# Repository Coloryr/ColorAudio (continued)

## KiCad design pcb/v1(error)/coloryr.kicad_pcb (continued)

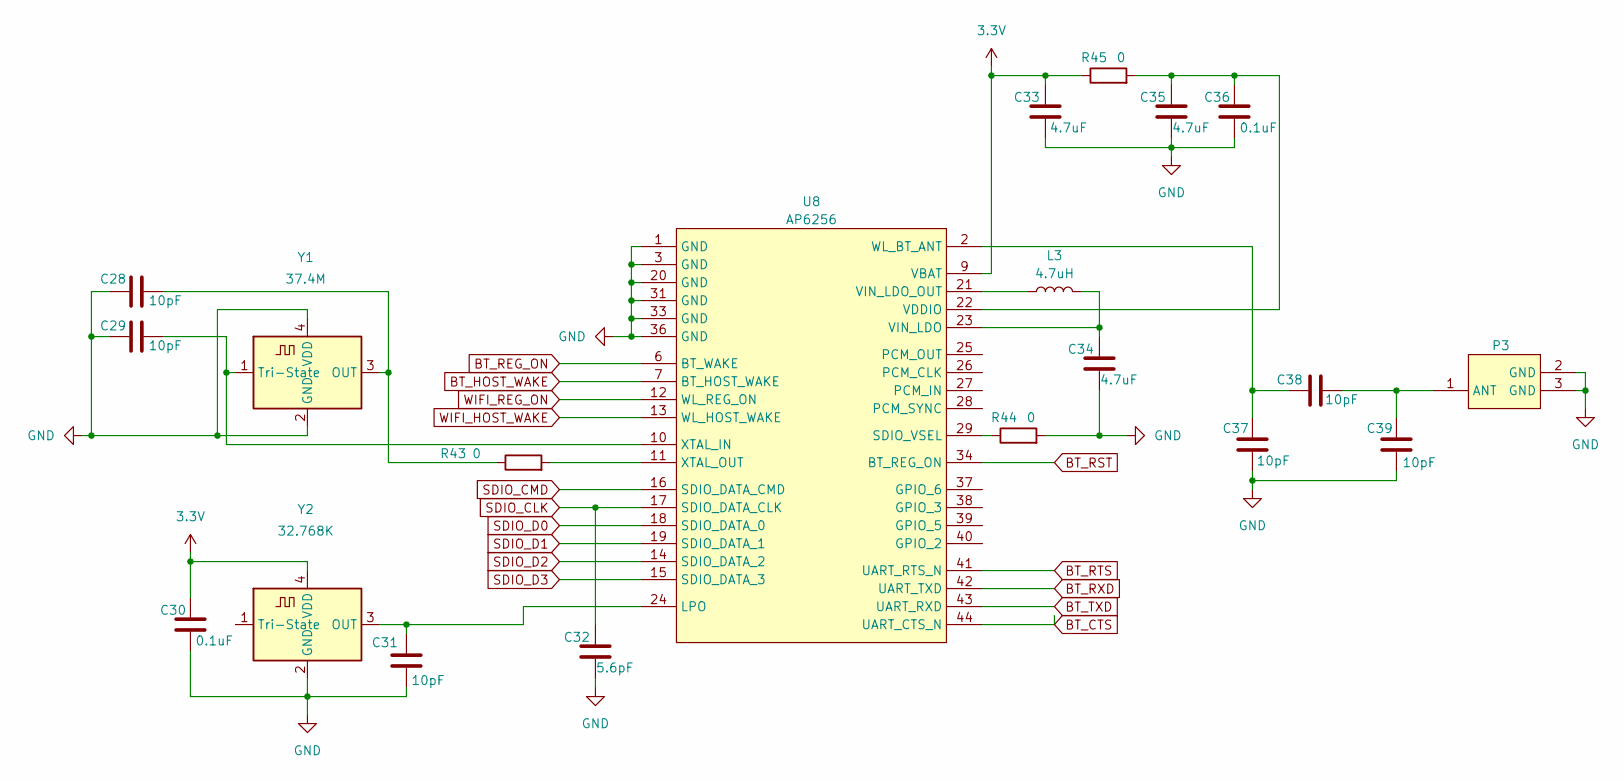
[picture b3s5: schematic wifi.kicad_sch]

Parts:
C28, C29, C31, C37, C38, C39: 10pF; C_0402_1005Metric_Pad0.74x0.62mm_HandSolder
C30, C36: 0.1uF; C_0402_1005Metric_Pad0.74x0.62mm_HandSolder
C32: 5.6pF; C_0402_1005Metric_Pad0.74x0.62mm_HandSolder
C33, C34, C35: 4.7uF; C_0402_1005Metric_Pad0.74x0.62mm_HandSolder
L3: 4.7uH; L_Murata_LQH2MCNxxxx02_2.0x1.6mm
P3: IPEX-SMD_BWIPX-1-001E
R43, R44, R45: 0; R_0402_1005Metric_Pad0.72x0.64mm_HandSolder
U8: AP6256
Y1: 37.4M; Oscillator_SMD_ECS_2520MV-xxx-xx-4Pin_2.5x2.0mm
Y2: 32.768K; Oscillator_SMD_ECS_2520MV-xxx-xx-4Pin_2.5x2.0mm

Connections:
3.3V: C30.2, C33.1, R45.1, U8.9 (VBAT), Y2.4 (VDD); also elsewhere on the board
BT_CTS: U8.44 (UART_CTS_N); also elsewhere on the board
BT_HOST_WAKE: U8.7 (BT_HOST_WAKE); also elsewhere on the board
BT_REG_ON: U8.6 (BT_WAKE); also elsewhere on the board
BT_RST: U8.34 (BT_REG_ON); also elsewhere on the board
BT_RTS: U8.41 (UART_RTS_N); also elsewhere on the board
BT_RXD: U8.42 (UART_TXD); also elsewhere on the board
BT_TXD: U8.43 (UART_RXD); also elsewhere on the board
GND: C28.1, C29.1, C30.1, C31.1, C32.2, C33.2, C34.2, C35.2, C36.1, C37.2, C39.2, P3.2 (GND), P3.3 (GND), R44.2, U8.1 (GND), U8.3 (GND), U8.20 (GND), U8.31 (GND), U8.33 (GND), U8.36 (GND), Y1.2 (GND), Y1.4 (VDD), Y2.2 (GND); also elsewhere on the board
unnamed: C38.1, C39.1, P3.1 (ANT)
unnamed: C31.2, U8.24 (LPO), Y2.3 (OUT)
unnamed: R44.1, U8.29 (SDIO_VSEL)
unnamed: C35.1, C36.2, R45.2, U8.22 (VDDIO)
unnamed: C34.1, L3.2, U8.23 (VIN_LDO)
unnamed: L3.1, U8.21 (VIN_LDO_OUT)
unnamed: C37.1, C38.2, U8.2 (WL_BT_ANT)
unnamed: C29.2, U8.10 (XTAL_IN), Y1.1 (Tri-State)
unnamed: R43.2, U8.11 (XTAL_OUT)
unnamed: C28.2, R43.1, Y1.3 (OUT)
SDIO_CLK: C32.1, U8.17 (SDIO_DATA_CLK); also elsewhere on the board
SDIO_CMD: U8.16 (SDIO_DATA_CMD); also elsewhere on the board
SDIO_D0: U8.18 (SDIO_DATA_0); also elsewhere on the board
SDIO_D1: U8.19 (SDIO_DATA_1); also elsewhere on the board
SDIO_D2: U8.14 (SDIO_DATA_2); also elsewhere on the board
SDIO_D3: U8.15 (SDIO_DATA_3); also elsewhere on the board
WIFI_HOST_WAKE: U8.13 (WL_HOST_WAKE); also elsewhere on the board
WIFI_REG_ON: U8.12 (WL_REG_ON); also elsewhere on the board

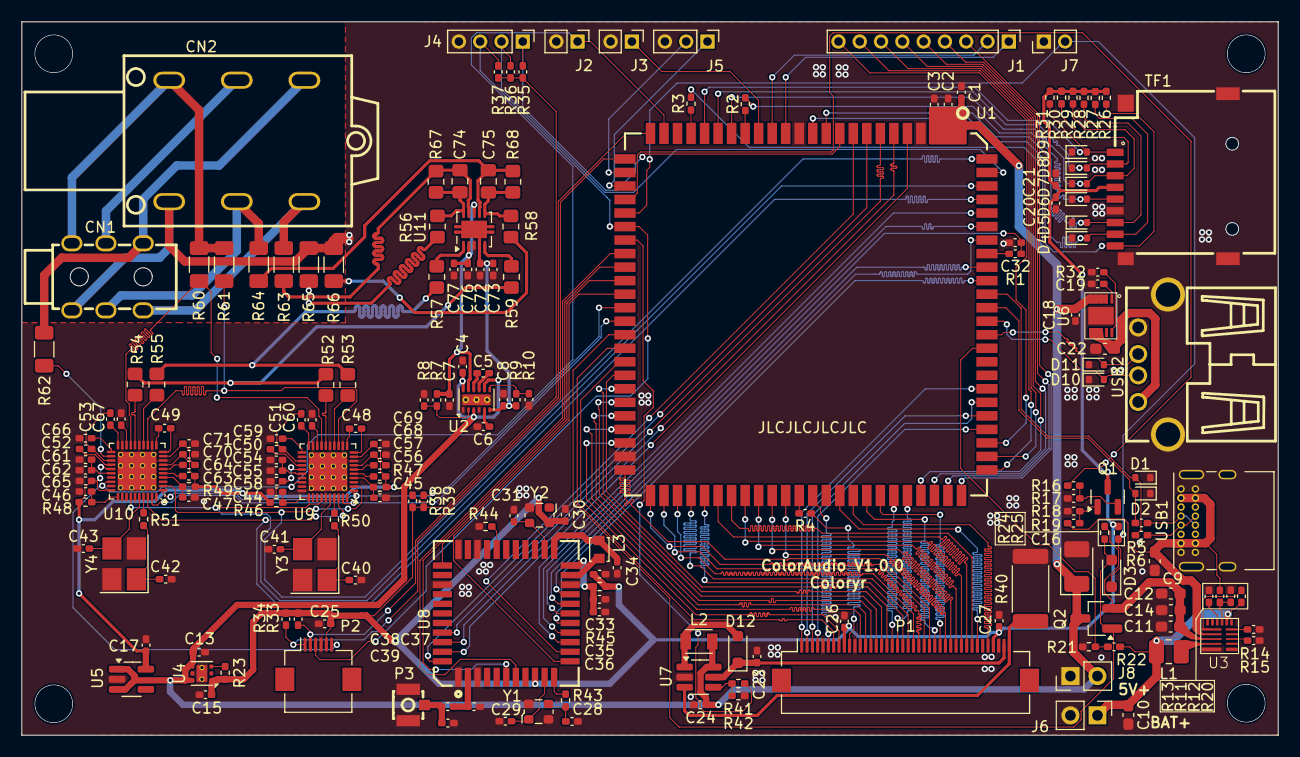
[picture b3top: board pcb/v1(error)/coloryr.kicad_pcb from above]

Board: 2 copper layers, 118.0 x 67.0 mm, 193 parts (0 on the bottom side), 186 nets.

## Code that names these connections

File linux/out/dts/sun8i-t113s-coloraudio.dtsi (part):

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
			/omit-if-no-ref/
			dsi_4lane_pins: dsi-4lane-pins {
				pins = "PD0", "PD1", "PD2", "PD3", "PD4", "PD5",
				       "PD6", "PD7", "PD8", "PD9";
				drive-strength = <30>;
				function = "dsi";
			};
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				function = "i2c2";
			};

			i2c2_pe12_pins: i2c2-pe12-pins {
				pins = "PE12", "PE13";
				function = "i2c2";
			};

			/omit-if-no-ref/
			lcd_rgb666_pins: lcd-rgb666-pins {
				pins = "PD0", "PD1", "PD2", "PD3", "PD4", "PD5",
				       "PD6", "PD7", "PD8", "PD9", "PD10", "PD11",
				       "PD12", "PD13", "PD14", "PD15", "PD16", "PD17",
				       "PD18", "PD19", "PD20", "PD21";
				function = "lcd0";
			};

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
			/omit-if-no-ref/
			mmc0_pins: mmc0-pins {
				pins = "PF0", "PF1", "PF2", "PF3", "PF4", "PF5";
				function = "mmc0";
			};

			/omit-if-no-ref/
			mmc1_pins: mmc1-pins {
				pins = "PG0", "PG1", "PG2", "PG3", "PG4", "PG5";
				function = "mmc1";
			};

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
			/omit-if-no-ref/
			rgmii_pe_pins: rgmii-pe-pins {
				pins = "PE0", "PE1", "PE2", "PE3", "PE4",
				       "PE5", "PE6", "PE7", "PE8", "PE9",
				       "PE11", "PE12", "PE13", "PE14", "PE15";
				function = "emac";
			};

			/omit-if-no-ref/
			rmii_pe_pins: rmii-pe-pins {
				pins = "PE0", "PE1", "PE2", "PE3", "PE4",
				       "PE5", "PE6", "PE7", "PE8", "PE9";
				function = "emac";
			};

			/omit-if-no-ref/
			pwm0_pd16_pin: pwm0-pd16-pin {
				pins = "PD16";
				function = "pwm0";
			};

			/omit-if-no-ref/
			pwm2_pd18_pin: pwm2-pd18-pin {
				pins = "PD18";
				function = "pwm2";
			};

			/omit-if-no-ref/
			pwm4_pd20_pin: pwm4-pd20-pin {
				pins = "PD20";
				function = "pwm4";
			};

			/omit-if-no-ref/
			pwm7_pd22_pin: pwm7-pd22-pin {
				pins = "PD22";
				function = "pwm7";
			};

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
			/omit-if-no-ref/
			spi1_pd_pins: spi1-pd-pins {
				pins = "PD10", "PD11", "PD12", "PD13", "PD14", "PD15";
				function = "spi1";
			};

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			};

			/omit-if-no-ref/
			uart0_pe2_pins: uart0-pe2-pins {
				pins = "PE2", "PE3";
				function = "uart0";
			};

			/omit-if-no-ref/
			uart1_pg6_pins: uart1-pg6-pins {
				pins = "PG6", "PG7";
				function = "uart1";
			};

			/omit-if-no-ref/
			uart1_pg8_rts_cts_pins: uart1-pg8-rts-cts-pins {
				pins = "PG8", "PG9";
				function = "uart1";
			};

			can0_pins: can0_pins@0 {
				pins = "PB2", "PB3";
				function = "can0";
				drive-strength = <10>;
				bias-pull-up;
			};

			can1_pins: can1_pins@0 {
				pins = "PB4", "PB5";
				function = "can1";
				drive-strength = <10>;
				bias-pull-up;
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
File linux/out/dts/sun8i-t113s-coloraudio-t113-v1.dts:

// SPDX-License-Identifier: (GPL-2.0+ OR MIT)
// Copyright (C) 2022 Arm Ltd.

/dts-v1/;

#include <dt-bindings/interrupt-controller/irq.h>
#include <dt-bindings/gpio/gpio.h>
#include "sun8i-t113s-coloraudio.dtsi"

/ {
	model = "ColorAudio V1-T113";
	compatible = "allwinner,sun20i-d1", "allwinner,sun8i";

	chosen {
		bootargs = "earlyprintk=sunxi-uart,0x02500000 mem=128M ubi.mtd=3 rootfstype=ubifs root=ubi0:rootfs rw rootwait console=ttyS0,115200";
		stdout-path = "serial0:115200n8";
	};

	aliases {
		serial0 = &uart0;
		// mmc0 = &mmc0;
		// mmc1 = &mmc1;      // AP6256 WiFi
        // mmc2 = &mmc2;      // TF卡
		// i2c1 = &i2c1;
		// i2c2 = &i2c2;
	};

	reg_vcc: vcc {
		compatible = "regulator-fixed";
		regulator-name = "vcc";
		regulator-min-microvolt = <5000000>;
		regulator-max-microvolt = <5000000>;
	};

	reg_usbvbus: usbvbus {
		compatible = "regulator-fixed";
		regulator-name = "usbvbus";
		regulator-min-microvolt = <5000000>;
		regulator-max-microvolt = <5000000>;
		vin-supply = <&reg_vcc>;
	};

	reg_vcc_3v3: vcc-3v3 {
		compatible = "regulator-fixed";
		regulator-name = "vcc-3v3";
		regulator-min-microvolt = <3300000>;
		regulator-max-microvolt = <3300000>;
		vin-supply = <&reg_vcc>;
	};

	reg_avdd2v8: avdd2v8 {
		compatible = "regulator-fixed";
		regulator-name = "avdd2v8";
		regulator-min-microvolt = <2800000>;
		regulator-max-microvolt = <2800000>;
		vin-supply = <&reg_vcc_3v3>;
	};

	reg_vdd_cpu: vdd-cpu {
		compatible = "regulator-fixed";
		regulator-name = "vdd-cpu";
		regulator-min-microvolt = <900000>;
		regulator-max-microvolt = <900000>;
		vin-supply = <&reg_vcc>;
	};

	leds {
		compatible = "gpio-leds";

		power {
			linux,default-trigger = "default-on";
			label = "power";
			gpios = <&pio 3 22 GPIO_ACTIVE_HIGH>;
		};
	};
};

&cpu0 {
	cpu-supply = <&reg_vdd_cpu>;
};

&cpu1 {
	cpu-supply = <&reg_vdd_cpu>;
};

// &wdt {
// 	status = "okay";
// };

// &ve {
// 	status = "disabled";
// };

&pio {
	vcc-pb-supply = <&reg_vcc_3v3>;
	vcc-pc-supply = <&reg_vcc_3v3>;
	vcc-pd-supply = <&reg_vcc_3v3>;
	vcc-pe-supply = <&reg_vcc_3v3>;
	vcc-pf-supply = <&reg_vcc_3v3>;
	vcc-pg-supply = <&reg_vcc_3v3>;

    i2c1_pins_a: i2c1@0 {
        pins = "PE0", "PE1";
        function = "i2c1";
    };

    i2c2_pins_a: i2c2@0 {
        pins = "PE12", "PE13";
        function = "i2c2";
    };

	rgb24_pins_a: rgb24@0 {
		allwinner,pins = "PB2", "PB3", "PD0", "PD1", "PD2", "PD3", "PD4", "PD5", \
			"PB4", "PB5", "PD6", "PD7", "PD8", "PD9", "PD10", "PD11", \
			"PB6", "PB7", "PD12", "PD13", "PD14", "PD15", "PD16", "PD17", \
			"PD18", "PD19", "PD20", "PD21";
		allwinner,pname = "lcdd0", "lcdd1", "lcdd2", "lcdd3", "lcdd4", "lcdd5", "lcdd6", "lcdd7", \
			"lcdd8", "lcdd9", "lcdd10", "lcdd11", "lcdd12", "lcdd13", "lcdd14", "lcdd15", \
			"lcdd16", "lcdd17", "lcdd18", "lcdd19", "lcdd20", "lcdd21", "lcdd22", "lcdd23", \
			"lcdclk", "lcdde", "lcdhsync", "lcdvsync";
		allwinner,function = "lcd0";
		allwinner,muxsel = <2>;
		allwinner,drive = <3>;
		allwinner,pull = <0>;
	};
	rgb24_pins_b: rgb24@1 {
		allwinner,pins = "PB2", "PB3", "PD0", "PD1", "PD2", "PD3", "PD4", "PD5", \
			"PB4", "PB5", "PD6", "PD7", "PD8", "PD9", "PD10", "PD11", \
			"PB6", "PB7", "PD12", "PD13", "PD14", "PD15", "PD16", "PD17", \
			"PD18", "PD19", "PD20", "PD21";
		allwinner,pname = "lcdd0", "lcdd1", "lcdd2", "lcdd3", "lcdd4", "lcdd5", "lcdd6", "lcdd7", \
			"lcdd8", "lcdd9", "lcdd10", "lcdd11", "lcdd12", "lcdd13", "lcdd14", "lcdd15", \
			"lcdd16", "lcdd17", "lcdd18", "lcdd19", "lcdd20", "lcdd21", "lcdd22", "lcdd23", \
			"lcdclk", "lcdde", "lcdhsync", "lcdvsync";
		allwinner,function = "io_disabled";
		allwinner,muxsel = <7>;
		allwinner,drive = <3>;
		allwinner,pull = <0>;
	};

	uart0_pins_a: uart0_pins@0 {
		pins = "PE2", "PE3";
		function = "uart0";
		drive-strength = <10>;
		bias-pull-up;
	};

	uart0_pins_b: uart0_pins@1 {
		pins = "PE2", "PE3";
		function = "gpio_in";
	};

	uart2_pins_a: uart2_pins@0 {
		pins = "PE2", "PE3";
		function = "uart2";
		drive-strength = <10>;
		bias-pull-up;
	};

	uart2_pins_b: uart2_pins@1 {
		pins = "PE2", "PE3";
		function = "gpio_in";
	};

	pwm2_pin_a: pwm2@0 {
		pins = "PE8";
		function = "pwm2";
		drive-strength = <10>;
		bias-pull-up;
	};

	pwm2_pin_b: pwm2@1 {
		pins = "PE8";
	};

	i2s1_pins_a: i2s1@0 {
		pins = "PG12","PG13","PG15";
		function = "i2s1";
		drive-strength = <20>;       
        bias-disable; 
	};

    rotary_pins: rotary-pins {
        pins = "PG11", "PG12";
        function = "gpio_in";
        bias-pull-up;
    };
};

&uart0 {
	pinctrl-names = "default", "sleep";
	pinctrl-0 = <&uart0_pins_a>;
	pinctrl-1 = <&uart0_pins_b>;
	status = "okay";
};

&uart1 {
	uart-has-rtscts;
	pinctrl-0 = <&uart1_pg6_pins>, <&uart1_pg8_rts_cts_pins>;
	pinctrl-names = "default";
	status = "okay";

	bluetooth {
		compatible = "brcm,bcm4345c5";
		device-wakeup-gpios = <&pio 4 6 GPIO_ACTIVE_HIGH>;
		host-wakeup-gpios = <&pio 4 7 GPIO_ACTIVE_HIGH>;
		shutdown-gpios = <&pio 4 5 GPIO_ACTIVE_HIGH>;
	};
};

&spi0 {
	pinctrl-0 = <&spi0_pins>;
	pinctrl-names = "default";
	status = "okay";

	spi_nand: spi_nand@0 {
        #address-cells = <1>;
        #size-cells = <1>;
		compatible = "spi-nand";
		reg = <0>;

		partition@0 {
			label = "awboot";
			reg = <0x0 0x40000>;	/* 256K */
			read-only;
		};

		partition@40000 {
			label = "dtb";
			reg = <0x40000 0x40000>;  /* 256k */
			read-only;
		};

		partition@80000 {
			label = "kernel";
			reg = <0x80000 0x780000>;  /* 7.5MB */
			read-only;
		};

		partition@800000 {
			label = "rootfs";
			reg = <0x800000 0x7800000>;
		};
	};
};

// &mmc0 {
// 	pinctrl-0 = <&mmc0_pins>;
// 	pinctrl-names = "default";
// 	vmmc-supply = <&reg_vcc_3v3>;
// 	vqmmc-supply = <&reg_vcc_3v3>;
// 	cd-gpios = <&pio 5 6 GPIO_ACTIVE_LOW>;
// 	disable-wp;
// 	bus-width = <4>;
// 	status = "okay";
// };

// &mmc1 {
// 	pinctrl-0 = <&mmc1_pins>;
// 	pinctrl-names = "default";
// 	vmmc-supply = <&reg_vcc_3v3>;
// 	vqmmc-supply = <&reg_vcc_3v3>;
// 	non-removable;
// 	bus-width = <4>;
// 	status = "okay";

// 	brcm: sdio-wifi@1 {
// 		reg = <1>;
// 		compatible = "brcm,bcm43456-sdio";
// 		brcm,drive-strength = <10>;
// 		wifi-reg-on-gpio = <&pio 4 4 GPIO_ACTIVE_HIGH>; 
//         host-wake-gpio = <&pio 3 10 GPIO_ACTIVE_HIGH>;
// 	};
// };

// &usbphy {
// 	usb0_vbus-supply = <&reg_usbvbus>;
// 	usb1_vbus-supply = <&reg_usbvbus>;
// 	status = "okay";
// };

// &usb_otg {
// 	dr_mode = "peripheral";
// 	status = "okay";
// };

// &dmic {
// 	status = "okay";
// };

// &ehci0 {
// 	status = "okay";
// };

// &ehci1 {
// 	dr_mode = "host";
// 	status = "okay";
// };

// &ohci0 {
// 	status = "okay";
// };

// &ohci1 {
// 	status = "okay";
// };

// &gpadc {
// 	channel_num = <1>;
// 	channel_select = <0x1>;
// 	channel_data_select = <0>;
// 	channel_compare_select = <0x1>;
// 	channel_cld_select = <0x1>;
// 	channel_chd_select = <0>;
// 	channel0_compare_lowdata = <1700000>;
// 	channel0_compare_higdata = <1200000>;
// 	channel1_compare_lowdata = <460000>;
// 	channel1_compare_higdata = <1200000>;
// 	status = "okay";
// };

// &tcon_lcd0 {
	
// 	/* part 1 */
// 	lcd_used            = <1>;
// 	lcd_driver_name     = "default_lcd";
// 	/* part 2 */
// 	lcd_if = <0>;
// 	lcd_hv_if = <0>;
// 	/* part 3 */
// 	lcd_x               = <854>;
// 	lcd_y               = <480>;
// 	lcd_width           = <154>;
// 	lcd_height          = <85>;

// 	lcd_dclk_freq       = <28>;
// 	lcd_hbp             = <30>;
// 	lcd_ht              = <902>;
// 	lcd_hspw            = <6>;
// 	lcd_vbp             = <30>;
// 	lcd_vt              = <523>;
// 	lcd_vspw            = <1>;

// 	/* part 5 */
// 	lcd_frm = <1>;
// 	lcd_io_phase = <0x0000>;
// 	lcd_gamma_en = <0>;
// 	lcd_cmap_en = <0>;
// 	lcd_hv_clk_phase = <0>;
// 	lcd_hv_sync_polarity= <0>;
				
// 	/* part 6 */
// 	lcd_power = "vcc-lcd";
// 	lcd_pin_power = "vcc-pd";
// 	pinctrl-0 = <&rgb24_pins_a>;
// 	pinctrl-1 = <&rgb24_pins_b>;
// };

// &pwm2 {
// 	pinctrl-names = "active", "sleep";
// 	pinctrl-0 = <&pwm2_pin_a>;
// 	pinctrl-1 = <&pwm2_pin_b>;
// 	status = "okay";
// };

// &i2c1 {
// 	pinctrl-0 = <&i2c1_pins_a>;
// 	pinctrl-names = "default";
// 	status = "okay";
// };

// &i2c2 {
// 	pinctrl-0 = <&i2c2_pins_a>;
// 	pinctrl-names = "default";
// 	status = "okay";
// };

// &i2s1 {
// 	tdm_config = <0x01>;
// 	pinctrl-names= "default";
// 	pinctrl-0 = <&i2s1_pins_a>;
// 	status = "okay";
// };

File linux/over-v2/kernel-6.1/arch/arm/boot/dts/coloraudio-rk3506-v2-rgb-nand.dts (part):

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			gpios = <&gpio3 RK_PA7 GPIO_ACTIVE_HIGH>;
			linux,default-trigger = "default-off";
			pinctrl-names = "default";
			pinctrl-0 = <&dac_reset_gpio>;
			default-state = "on";
		};
		wifi_power: wifi-power {
			gpios = <&gpio0 RK_PB1 GPIO_ACTIVE_HIGH>;
			linux,default-trigger = "default-off";
			pinctrl-names = "default";
			pinctrl-0 = <&wifi_power_gpio>;
			default-state = "on";
		};
    };
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		enable-gpios = <&gpio2 RK_PB6 GPIO_ACTIVE_HIGH>;
		enable-delay-ms = <20>;
		pinctrl-names = "default";
		pinctrl-0 = <&lcd_en_gpio>;
		display-timings {
			native-mode = <&timing0>;
			timing0: timing0 {
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
&pinctrl {
	lcd {
		lcd_en_gpio: lcd-en-gpio {
			rockchip,pins = <2 RK_PB6 RK_FUNC_GPIO &pcfg_pull_none>;
		};
	};
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    };

	wifi {
		wifi_power_gpio: wifi-power-gpio {
			rockchip,pins = <0 RK_PB1 RK_FUNC_GPIO &pcfg_pull_none>;
		};
    };
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		dac_gpio: dac-gpio {
			rockchip,pins = <0 RK_PB4 RK_FUNC_GPIO &pcfg_pull_none>;
		};
		dac_reset_gpio: dac-reset-gpio {
			rockchip,pins = <3 RK_PA7 RK_FUNC_GPIO &pcfg_pull_up>;
		};
	};
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	cd-gpios = <&gpio3 RK_PA6 GPIO_ACTIVE_LOW>;
	disable-wp;
	pinctrl-names = "default";
	pinctrl-0 = <&sdmmc_clk_pins &sdmmc_cmd_pins &sdmmc_bus4_pins &sd_det>;
	status = "okay";
};

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
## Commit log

2025-04-21 init
2025-04-21 Create LICENSE
2025-04-22 up dts
2025-05-26 up fix lcd pcb
2025-06-03 up pcb
2025-06-03 add patch
2025-06-04 up dac ok
2025-06-18 up v3
2025-06-26 up pcb v3.2
2025-06-26 up mipi ok
2025-06-27 up use new driver
2025-07-01 up use c++
2025-07-04 up use api
2025-07-06 up v3 ok
2025-07-06 up v3 linux
2025-07-06 up ui
2025-07-06 up change fft
2025-07-09 up lyric new draw
2025-07-09 up config
2025-07-14 up add bluez-alsa
2025-07-20 uac2 mt ssize
2025-07-20 up uac
2025-07-21 up uac1 remove mt size
2025-07-24 up move
2025-08-11 up bug
2025-08-12 up usb audio
2025-09-04 up 3.1hw
2025-09-10 Update rockchip_rk3506_coloraudio_buildroot_defconfig
2026-01-27 up pcb 3.8
2026-02-03 pcb 3.9
2026-02-04 linux
2026-02-06 dac int
2026-02-11 3.11
